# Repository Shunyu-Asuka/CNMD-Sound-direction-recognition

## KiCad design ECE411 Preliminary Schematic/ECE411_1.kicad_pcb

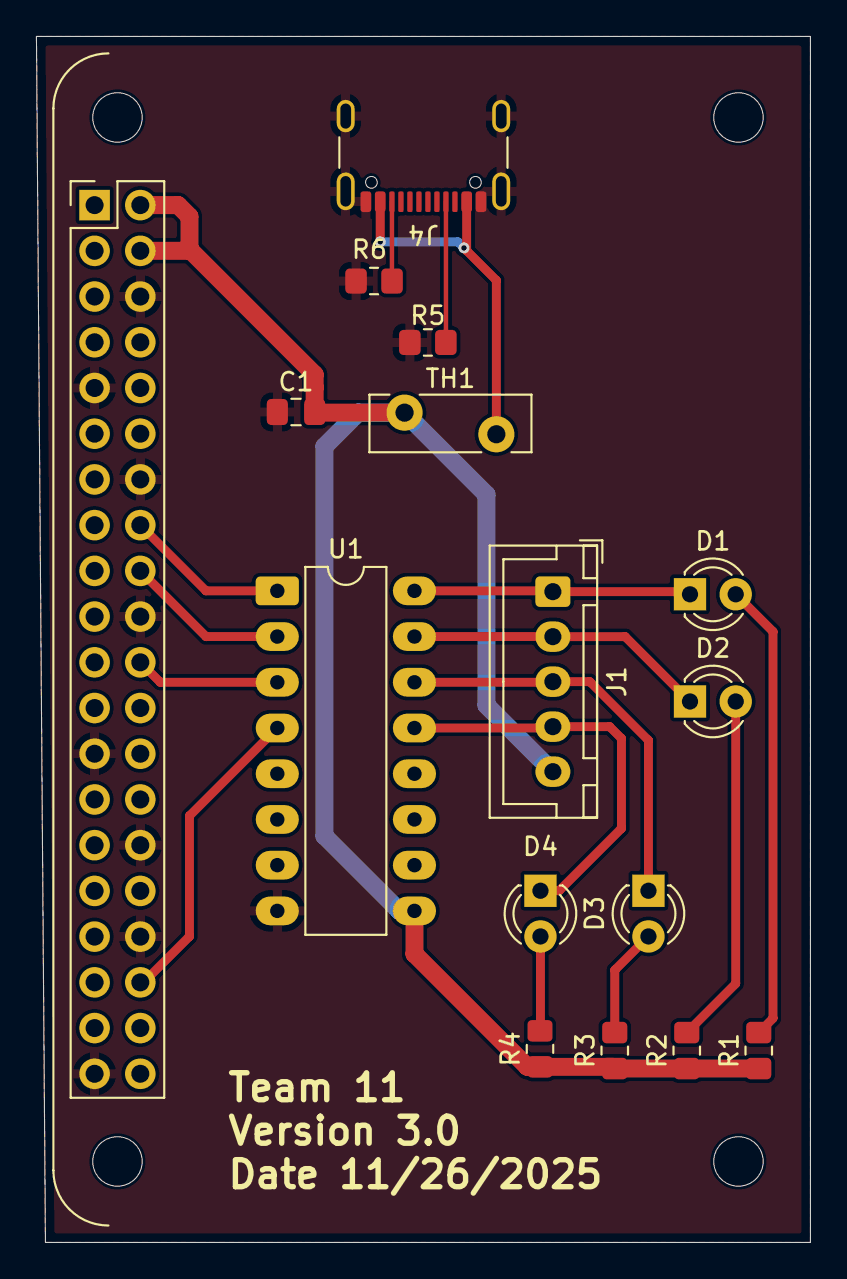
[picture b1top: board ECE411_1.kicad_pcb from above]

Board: 2 copper layers, 43.0 x 67.0 mm, 16 parts (0 on the bottom side), 17 nets.

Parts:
C1: 100nF; C_0805_2012Metric_Pad1.18x1.45mm_HandSolder
D1, D2, D3, D4: LED; LED_D3.0mm
J1: Conn_01x05; JST_XH_B5B-XH-A_1x05_P2.50mm_Vertical
J2: Raspberry_Pi_4; rap5
J4: USB_C_Receptacle_USB2.0_16P; USB_C_Receptacle_GCT_USB4105-xx-A_16P_TopMnt_Horizontal
R1, R2, R3, R4: 0.5k; R_0805_2012Metric_Pad1.20x1.40mm_HandSolder
R5, R6: 5.1k; R_0805_2012Metric_Pad1.20x1.40mm_HandSolder
TH1: Thermistor_PTC; Fuse_Bourns_MF-RHT300
U1: ULN2003; DIP-16_W7.62mm_LongPads

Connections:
/VCC: C1.2, J1.5, J2.2 (5V), J2.4 (5V), R1.1, R2.1, R3.1, R4.1, TH1.1, U1.9 (COM)
GND: C1.1, J2.6 (GND), J2.9 (GND), J2.14 (GND), J2.20 (GND), J2.25 (GND), J2.30 (GND), J2.34 (GND), J2.39 (GND), J4.A1 (GND), J4.A12 (GND), J4.B1 (GND), J4.B12 (GND), J4.S1 (SHIELD), R5.2, R6.2, U1.8 (GND)
IN1: J2.16 (GPIO23/SDIO_CMD), U1.1 (I1)
IN2: J2.18 (GPIO24/SDIO_DAT0), U1.2 (I2)
IN3: J2.22 (GPIO25/SDIO_DAT1), U1.3 (I3)
IN4: J2.36 (GPIO16/SPI1_~CE2), U1.4 (I4)
unnamed: D1.2 (A), R1.2
unnamed: D1.1 (K), J1.1, U1.16 (O1)
unnamed: D2.2 (A), R2.2
unnamed: D2.1 (K), J1.2, U1.15 (O2)
unnamed: D3.2 (A), R3.2
unnamed: D3.1 (K), J1.3, U1.14 (O3)
unnamed: D4.2 (A), R4.2
unnamed: D4.1 (K), J1.4, U1.13 (O4)
unnamed: J4.A5 (CC1), R5.1
unnamed: J4.B5 (CC2), R6.1
unnamed: J4.A4 (VBUS), J4.A9 (VBUS), J4.B4 (VBUS), J4.B9 (VBUS), TH1.2
